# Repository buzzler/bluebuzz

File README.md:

# BlueBuzz

BlueBuzz is an ESP32-based controller that bridges Bluetooth Gamepads, Keyboards, and Mice to MSX computers via GPIO pins. It supports multiple input modes and can be updated over-the-air (OTA).

## Features

- **Multi-Mode Support**:
  - Gamepad mode with turbo buttons
  - Keyboard mode for MSX keyboard emulation
  - Mouse mode for MSX mouse support
- **Bluetooth Connectivity**:
  - Automatic pairing with Bluetooth controllers
  - Support for multiple controller types
- **OTA Updates**: Over-the-air firmware updates via web interface
- **Rumble Feedback**: Vibration feedback for gamepad input
- **LED Indicators**: Visual status feedback

## Hardware Requirements

- ESP32 development board
- Bluetooth controller (compatible with Bluepad32)
- MSX computer with GPIO expansion capability
- 10kΩ pull-up resistors for buttons (if needed)

## Pin Configuration

| Function | GPIO |
|----------|------|
| UP Button | 14 |
| DOWN Button | 26 |
| LEFT Button | 33 |
| RIGHT Button | 32 |
| A Button | 27 |
| B Button | 25 |
| OUT Signal | 17 |
| LED Indicator | 18 |

## Modes of Operation

### Gamepad Mode
- Supports standard gamepad controls
- Turbo buttons (L1/R1) for adjustable rapid fire
- D-Pad and analog stick support

### Keyboard Mode
- Emulates MSX keyboard input
- Arrow keys and WASD for movement
- N/Space/Enter for action buttons
- M/Esc for secondary actions

### Mouse Mode
- Converts controller mouse movements to MSX mouse input
- Button mapping for left/right/middle clicks
- Scroll wheel support

## Setup Instructions

1. Install required libraries:
   - ESP32 Board Support
   - Bluepad32
   - ESPAsyncWebServer
   - ElegantOTA

2. Upload firmware to ESP32 board

3. Connect to WiFi network "BlueBuzz" (default password: none)

4. Access OTA update interface at `http://192.168.1.1/update`

## Usage

### Connecting Controllers
1. Power on BlueBuzz
2. Press and hold SELECT+START on controller for 3 seconds to enter pairing mode
3. Pair with your Bluetooth controller

### Switching Modes
- **Pairing Mode**: SELECT + START (up)
- **OTA Update**: SELECT + START (down)

## Technical Details

### State Machine
The device uses a state machine to manage different operational modes:
1. INIT - System initialization
2. PAIRING - Bluetooth pairing mode
3. CONNECTED - Waiting for controller connection
4. GAMEPAD - Gamepad input processing
5. KEYBOARD - Keyboard input processing
6. MOUSE - Mouse input processing
7. OTA - Over-the-air update mode
8. ERROR - Error handling

### Input Processing
- Gamepad: Direct button mapping with turbo functionality
- Keyboard: Key mapping to MSX keyboard codes
- Mouse: Relative movement conversion to MSX mouse commands

### Power Management
- CPU frequency set to 80MHz for stability
- Efficient power usage in idle states

## Troubleshooting

### Common Issues
1. **Controller not connecting**:
   - Ensure device is in pairing mode (LED blinking)
   - Check Bluetooth compatibility
   - Try forgetting previous connections

2. **No input detection**:
   - Verify pin connections
   - Confirm controller is properly paired
   - Check MSX GPIO configuration

3. **OTA Update fails**:
   - Ensure stable WiFi connection
   - Verify correct firmware file
   - Check available storage space

## License

This project is licensed under the GNU General Public License v3.0 (GPL-3.0).

## Acknowledgments

- Uses Bluepad32 library for Bluetooth controller support
- ESPAsyncWebServer and ElegantOTA for OTA updates

- Inspired by MSX computing community projects

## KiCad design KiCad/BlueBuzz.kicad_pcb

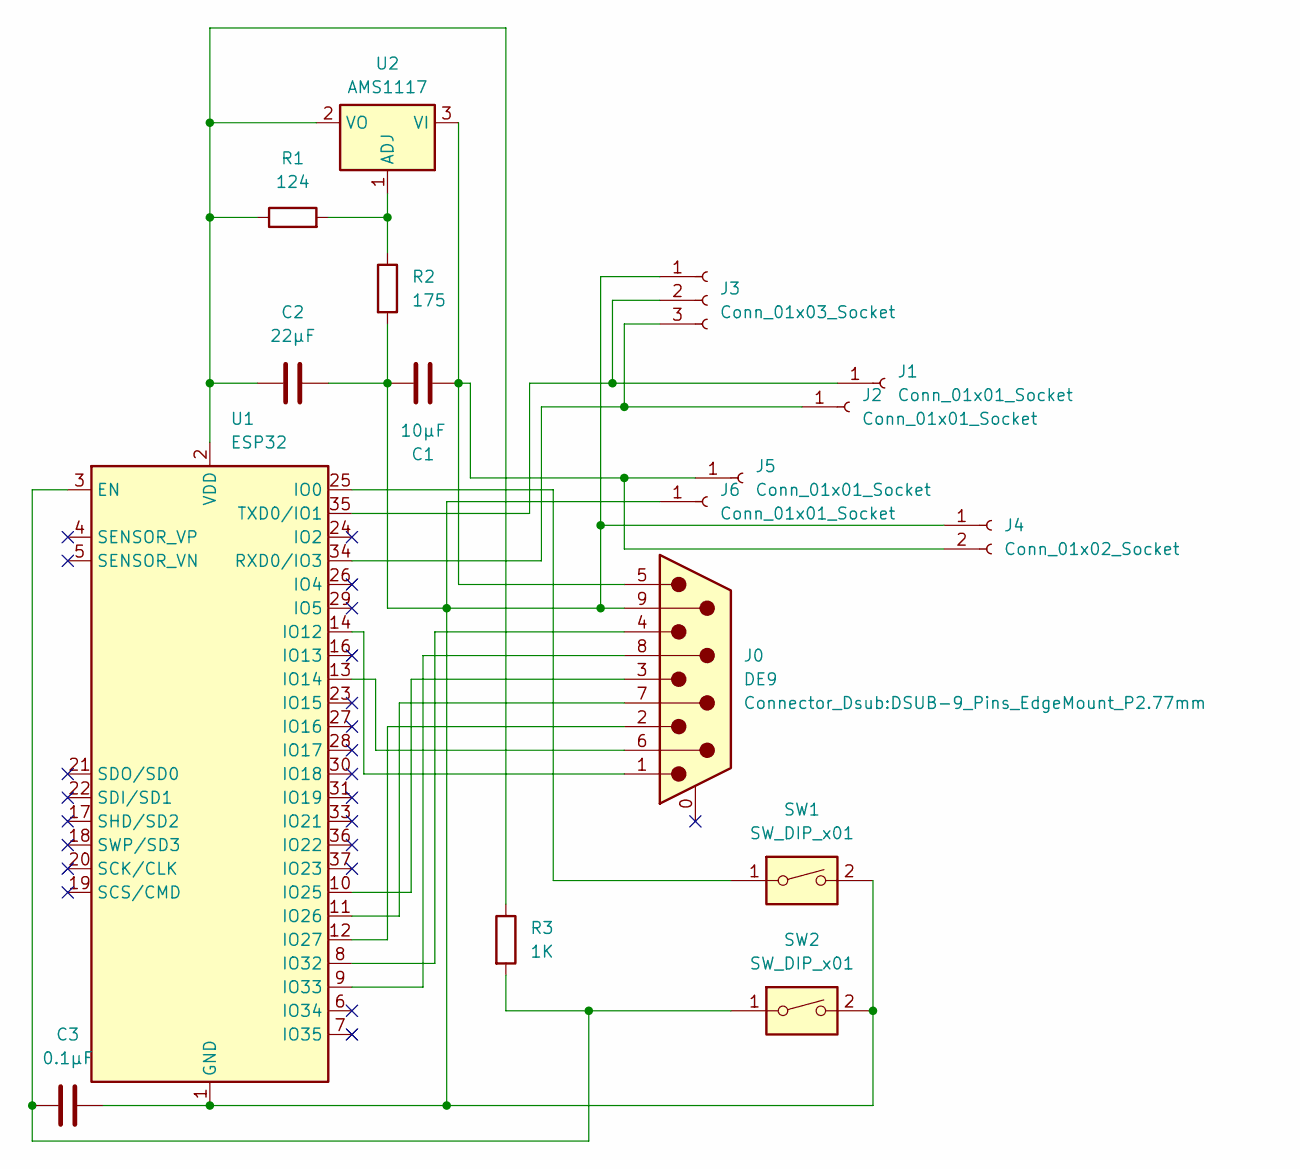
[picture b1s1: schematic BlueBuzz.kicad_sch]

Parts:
C1: 10μF; C_0805_2012Metric
C2: 22μF; C_0805_2012Metric
C3: 0.1μF; C_0805_2012Metric
J0: DE9; DSUB-9_Pins_EdgeMount_P2.77mm
J1, J2, J5, J6: Conn_01x01_Socket; SolderWirePad_1x01_SMD_1x2mm
J3: Conn_01x03_Socket; SolderJumper-3_P1.3mm_Open_Pad1.0x1.5mm_NumberLabels
J4: Conn_01x02_Socket; SolderJumper-2_P1.3mm_Open_Pad1.0x1.5mm
R1: 124; R_0805_2012Metric
R2: 175; R_0805_2012Metric
R3: 1K; R_0805_2012Metric
SW1, SW2: SW_DIP_x01; SW_Tactile_SPST_NO_Straight_CK_PTS636Sx25SMTRLFS
U1: ESP32; ESP32-WROOM-32
U2: AMS1117; SOT-223-3_TabPin2

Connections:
unnamed: J1.1, J3.2, U1.35 (TXD0/IO1)
unnamed: J2.1, J3.3, U1.34 (RXD0/IO3)
unnamed: C1.1, C2.1, C3.2, J0.9, J3.1, J4.1, J6.1, R2.2, SW1.2, SW2.2, U1.1 (GND), U1.15 (GND), U1.38 (GND), U1.39 (GND)
unnamed: C1.2, J0.5, J4.2, J5.1, U2.3 (VI)
unnamed: C3.1, R3.2, SW2.1, U1.3 (EN)
unnamed: SW1.1, U1.25 (IO0)
unnamed: J0.1, U1.14 (IO12)
unnamed: J0.6, U1.13 (IO14)
unnamed: J0.3, U1.10 (IO25)
unnamed: J0.7, U1.11 (IO26)
unnamed: J0.2, U1.12 (IO27)
unnamed: J0.4, U1.8 (IO32)
unnamed: J0.8, U1.9 (IO33)
unnamed: C2.2, R1.1, R3.1, U1.2 (VDD), U2.2 (VO)
unnamed: R1.2, R2.1, U2.1 (ADJ)

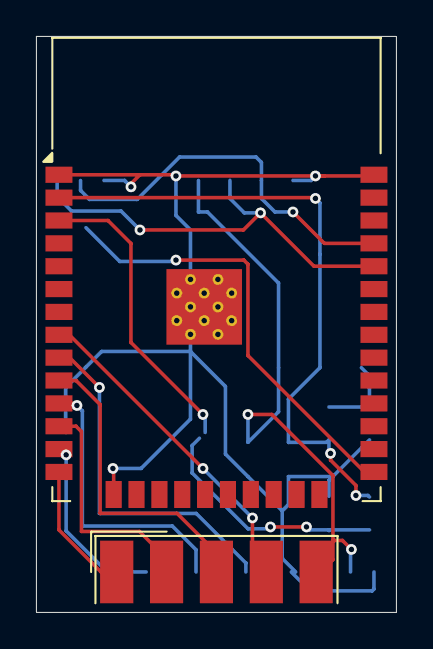
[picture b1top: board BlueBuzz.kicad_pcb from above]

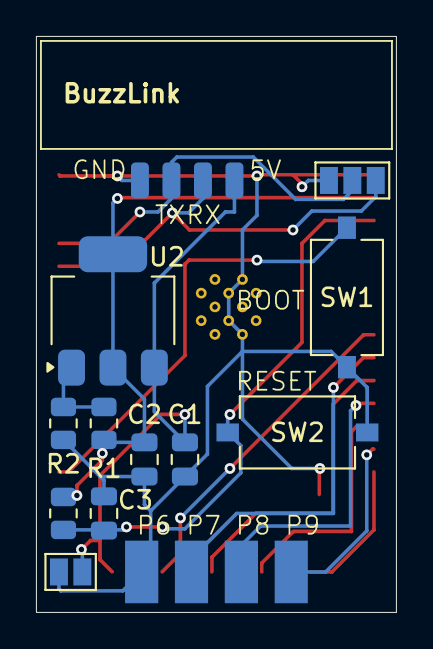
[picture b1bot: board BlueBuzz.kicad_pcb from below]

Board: 2 copper layers, 20.0 x 32.0 mm, 17 parts (15 on the bottom side), 15 nets.

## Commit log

2025-07-31 two controller support on TinyPICO
2025-08-01 support mouse emulation
2025-08-02 support msx mouse
2025-08-02 fixed PLAYER index bug
2025-08-03 update Licence
2025-08-20 add schematics for kicad
2025-08-20 add rendered PCB
2025-08-20 update PCB
2025-09-05 상태표시 LED 추가. 입력 전압 3.3V 변환 로직 추가. 핀배열 변경. 사용법 변경.
2025-09-05 add rendered schematic
2025-09-05 fixed compile error
2025-09-05 OTA 지원
2025-09-06 refactoring..
2025-09-06 new docstrings
2025-09-08 fixed turbo counter error
